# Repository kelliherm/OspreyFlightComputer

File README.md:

# Osprey Flight Computer

The Osprey Flight Computer is a flight computer based on the Raspberry Pi Pico, designed for use in small scale model rocketry. Osprey features the RP2040, MPU-6050, and BMP280 as it's primary ICs.

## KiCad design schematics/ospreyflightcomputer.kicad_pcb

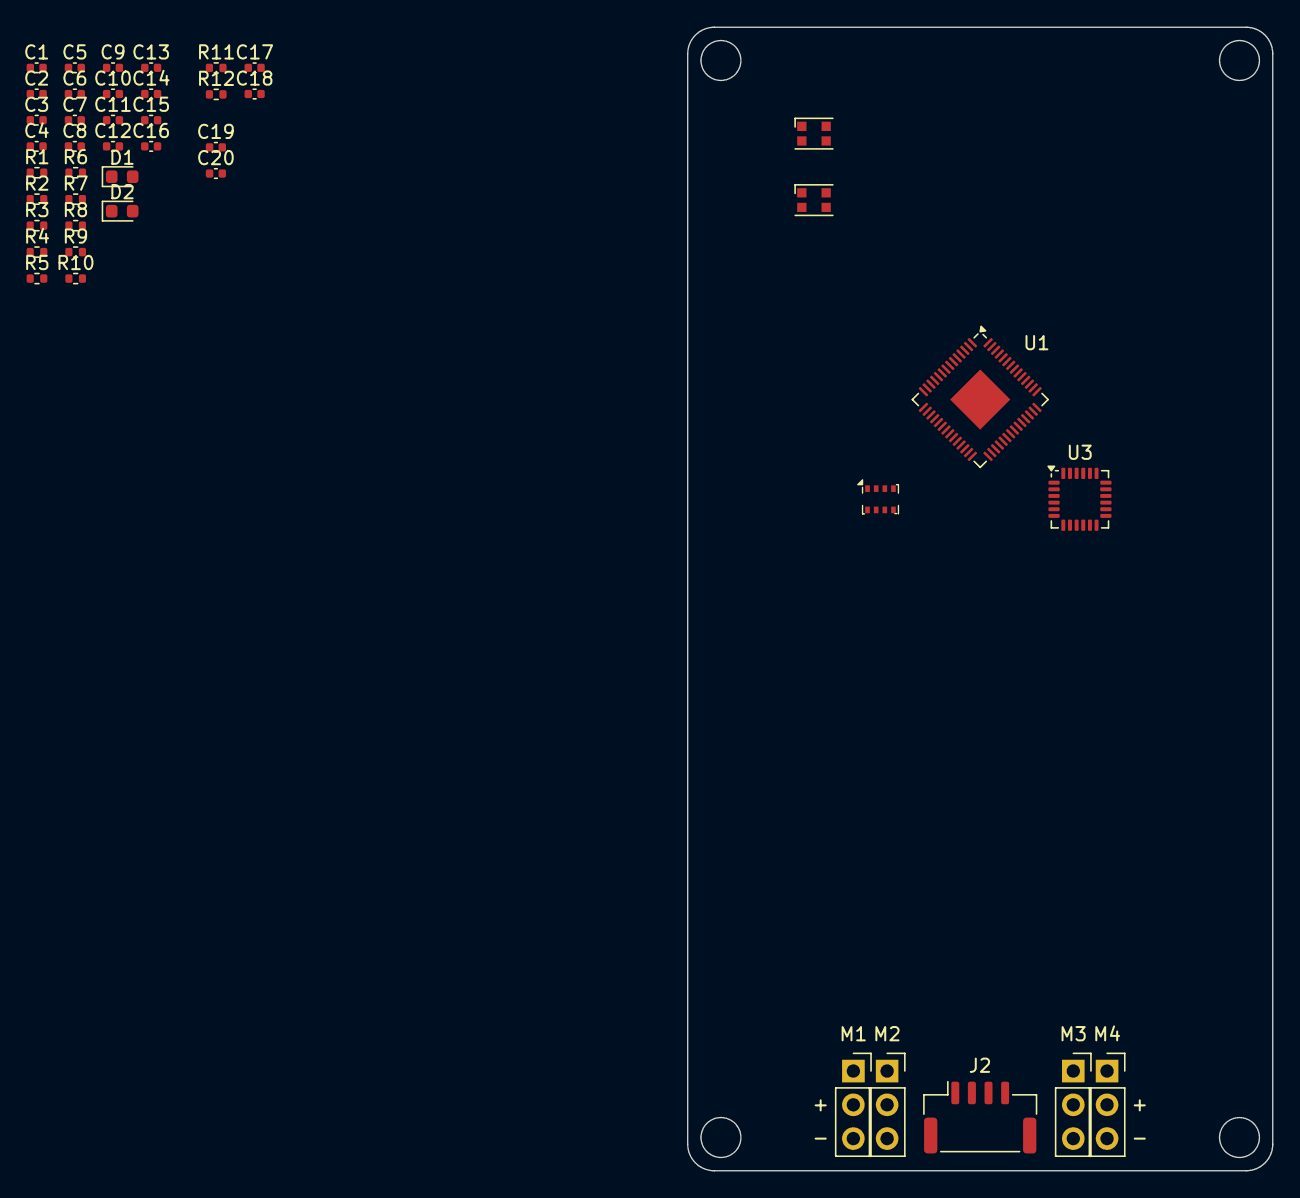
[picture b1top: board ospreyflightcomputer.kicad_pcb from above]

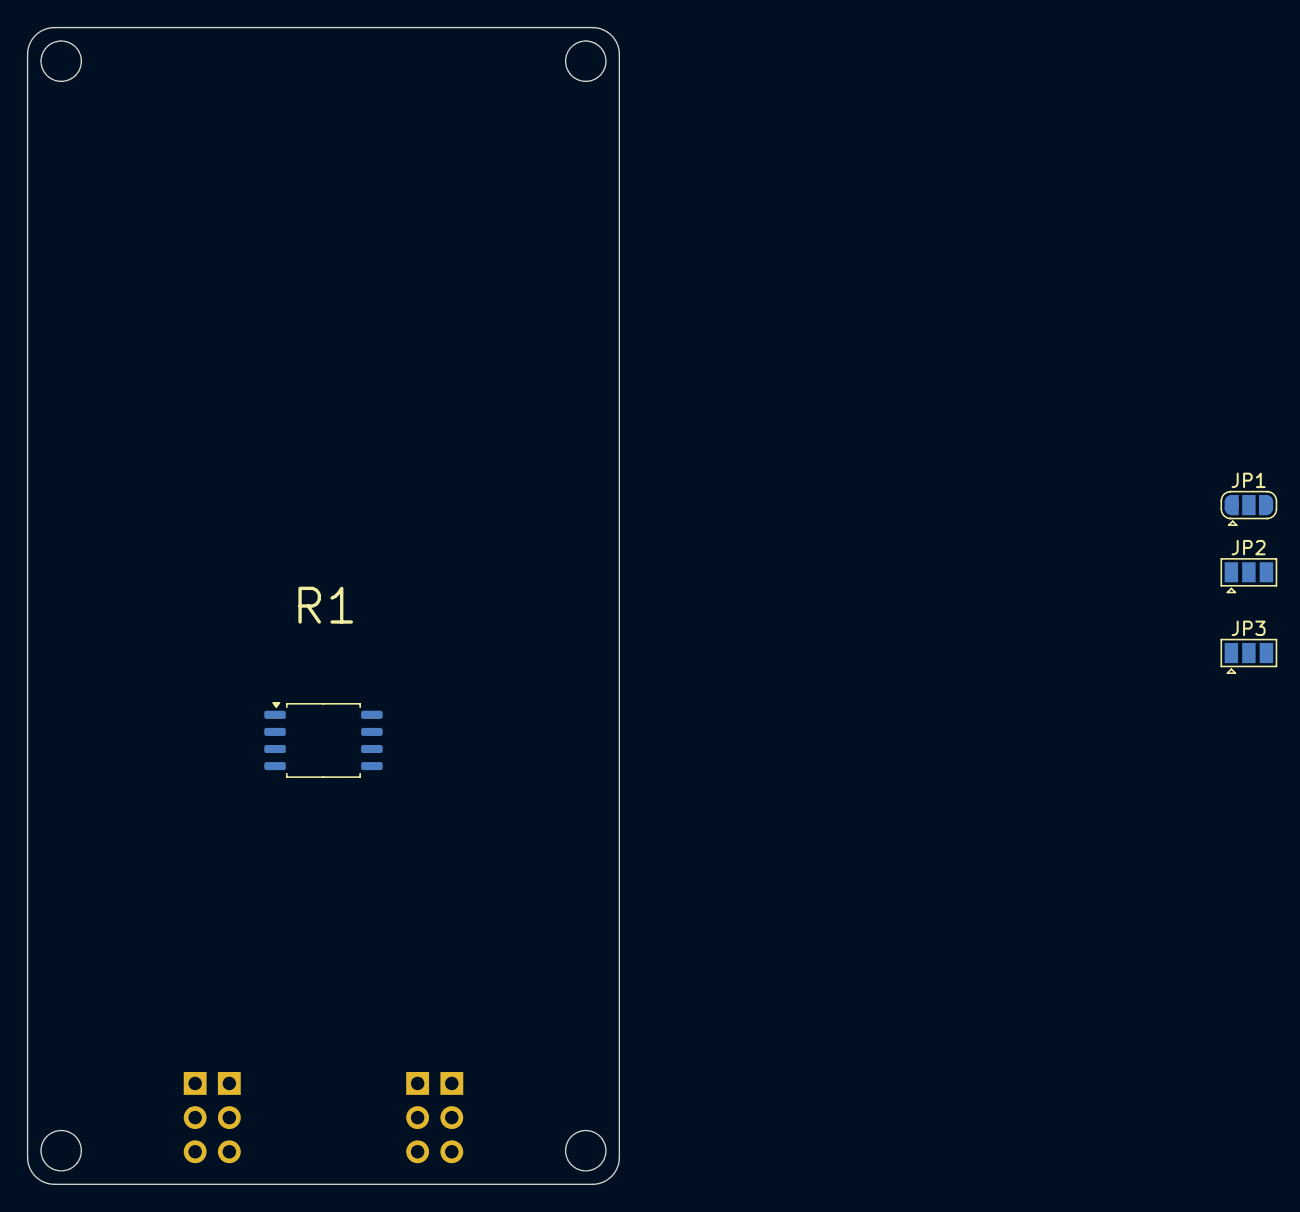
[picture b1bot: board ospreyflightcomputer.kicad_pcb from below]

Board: 2 copper layers, 44.0 x 86.0 mm, 48 parts (4 on the bottom side), 27 nets, no tracks yet.

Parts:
C1, C2: 15pF; C_0402_1005Metric
C3, C15: 2.2uF; C_0402_1005Metric
C4, C5, C6, C7, C8, C9, C10, C11, C12, C13, C14, C16, C17, C18, C19, C20: 0.1uF; C_0402_1005Metric
D1: Blue; LED_0603_1608Metric
D2: Green; LED_0603_1608Metric
D3: WS2812B-A; LED_WS2812B-2020_PLCC4_2.0x2.0mm
D4: WS2812B-B; LED_WS2812B-2020_PLCC4_2.0x2.0mm
J2: I2C JST; JST_GH_SM04B-GHS-TB_1x04-1MP_P1.25mm_Horizontal
JP1: SolderJumper_3_Bridged123; SolderJumper-3_P1.3mm_Open_RoundedPad1.0x1.5mm
JP2, JP3: Servo PWR; SolderJumper-3_P1.3mm_Open_Pad1.0x1.5mm
M1: Servo X; PinSocket_1x03_P2.54mm_Vertical
M2: Servo Y; PinSocket_1x03_P2.54mm_Vertical
M3: Servo A; PinSocket_1x03_P2.54mm_Vertical
M4: Servo B; PinSocket_1x03_P2.54mm_Vertical
R1, R5, R6, R10: 1K; R_0402_1005Metric
R2, R3, R4: R; R_0402_1005Metric
R7, R8: 5.1K; R_0402_1005Metric
R9: 10K; R_0402_1005Metric
R11, R12: 2.2K; R_0402_1005Metric
U1: RP2040; QFN-56-1EP_7x7mm_P0.4mm_EP3.2x3.2mm
U2: W25Q16JVSS; SOIC-8_5.23x5.23mm_P1.27mm
U3: MPU-6050; InvenSense_QFN-24_4x4mm_P0.5mm
U4: BMP280; Bosch_LGA-8_2x2.5mm_P0.65mm_ClockwisePinNumbering

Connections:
+1.1V: C11.1, C12.1, C13.1, U1.23 (DVDD), U1.45 (VREG_VOUT), U1.50 (DVDD)
+3.3V: C4.1, C5.1, C6.1, C7.1, C8.1, C9.1, C10.1, C14.1, C15.1, C16.1, C17.1, C18.1, D2.2 (A), D3.4 (VDD), D4.4 (VDD), J2.2, JP1.2 (C), R2.2, R9.1, U1.1 (IOVDD), U1.10 (IOVDD), U1.22 (IOVDD), U1.33 (IOVDD), U1.42 (IOVDD), U1.44 (VREG_IN), U1.48 (USB_VDD), U1.49 (IOVDD), U2.8 (VCC), U3.8 (VLOGIC), U3.13 (VDD), U4.6 (VDDIO), U4.8 (VDD)
+5V: JP2.1 (A), JP3.1 (A)
+7.5V: JP2.3 (B), JP3.3 (B)
/Main Processing Unit/LED_BUILTIN: D1.2 (A), U1.37 (GPIO25)
/Main Processing Unit/QSPI-CS: R9.2, R10.2, U2.1 (~CS)
AVDD: C3.1, R2.1, U1.43 (ADC_AVDD)
GND: C1.2, C2.2, C3.2, C4.2, C5.2, C6.2, C7.2, C8.2, C9.2, C10.2, C11.2, C12.2, C13.2, C14.2, C15.2, C16.2, C17.2, C18.2, C19.1, C20.1, D3.2 (VSS), D4.2 (VSS), J2.1, M1.3 (-), M2.3 (-), M3.3 (-), M4.3 (-), R5.2, R6.2, R7.2, R8.2, U1.57 (GND), U2.4 (GND), U3.18 (GND), U4.1 (GND), U4.7 (GND)
I2C1_SCL: J2.4, R11.1, U1.9 (GPIO7), U3.23 (SCL), U4.4 (SCK)
I2C1_SDA: J2.3, R12.1, U1.8 (GPIO6), U3.24 (SDA), U4.3 (SDI)
IMU_AD0: U1.2 (GPIO0), U3.9 (AD0)
IMU_INT: U1.3 (GPIO1), U3.12 (INT)
unnamed: C2.1, R1.1
unnamed: D1.1 (K), R5.1
unnamed: D2.1 (K), R6.1
unnamed: JP1.1 (A), R12.2
unnamed: JP1.3 (B), R11.2
unnamed: JP2.2 (C), M1.2 (+), M2.2 (+)
unnamed: JP3.2 (C), M3.2 (+), M4.2 (+)
unnamed: R4.2, U1.46 (USB_DM)
unnamed: R3.2, U1.47 (USB_DP)
unnamed: C1.1, U1.20 (XIN)
unnamed: R1.2, U1.21 (XOUT)
unnamed: C19.2, U3.20 (CPOUT)
unnamed: C20.2, U3.10 (REGOUT)
RGB_A: D3.3 (DIN), U1.6 (GPIO4)
RGB_B: D4.3 (DIN), U1.7 (GPIO5)

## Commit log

2024-11-03 Added thrust curve data
2024-11-03 Fixed typo
2024-11-03 Added working schematic and pcb files
2024-11-03 Reformatted CSV files
